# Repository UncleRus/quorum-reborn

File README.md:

# Quorum Reborn

## Russian

[English](#english)

Старая и восстановленная документация для компьютеров ZX Spectrum "Кворум" и "Магик".

### Что такое "Кворум"?

"Кворум" — домашний компьютер, клон ZX Spectrum на советской элементной базе.
Разработан в Свердловске/Екатеринбурге Камилем Каримовым, выпускался заводами
"Вектор", "УОМЗ". Все машины имеют кодер SECAM.

Поддержка "Кворума" встроена в эмуляторы UnrealSpeccy и ZXMAK2.

#### Модели компьютеров

- **Magic-05** — Клон ZX Spectrum 48K с расширенной клавиатурой и портом Centronics.
- **Кворум 64** — Модифицированная версия «Magic-05» с доступным ОЗУ объёмом 64 КБ
   (дополнительные 16 КБ использовались как «теневое» ОЗУ) и измененной адресацией
   дополнительного порта расширенной клавиатуры.
- **Кворум 128** — Клон ZX Spectrum 128K без AY-3-8910. Схема построена на БМК
   КБ01ВГ1-2. В ПЗУ присутствует встроенный тест, монитор и копировщик. Возможность
   работы как в TR-DOS, так и в CP/M. На задней стенке корпуса компьютера располагались
   разъёмы для подключения внешнего блока питания, Kempston и Sinclair джойстиков,
   принтера, магнитофона, телевизора и монитора, а также разъём системной шины для
   подключения внешнего контроллера дисковода.
- **Кворум 128+** — Модификация «Кворум 128» со встроенным 3-дюймовым дисководом,
   контроллером дисковода и звуковым синтезатором AY-3-8910.
- **Кворум БК04** — Выпускался УОМЗ. Клон ZX Spectrum 48K. Имеет кодер SECAM с
   ВЧ-модулятором.
- **Кворум БК05** — Выпускался УОМЗ. Клон ZX Spectrum 48K на БМК КБ01ВГ1-2 и
   однокристальном SECAM-кодере. На плате реализован порт принтера, но отсутствует
   разъем.

### Состав репозитория

- **kicad** - Проекты KiCad для
   - Magic-05,
   - Кворум 64,
   - Кворум 128,
   - Кворум БК04,
   - контроллера дисковода
- **resources** - Старая документация, прошивки, фотографии, софт

### Проекты KiCad

Для работы с ними необходим KiCad версии >= 7.0.
Также в каждом проекте, в подкаталогах /plot лежат схемы, экспортированные в формат PDF.

### Ссылки

https://github.com/atsidaev/quorum-cpm - Исходники CP/M для "Кворума", документация 
по программированию.

## English

Old and restored documentation for ZX Spectrum computers "Quorum" and "Magic".

### What is "Quorum"?

"Quorum" is a home computer, a clone of the ZX Spectrum built with Soviet ICs.
It's developed in Yekaterinburg f.k.a. Sverdlovsk by Kamil Karimov and manufactured by "Vector" and "UOMZ"
factories. All models have built-in SECAM encoder.

Quorum is supported by UnrealSpeccy and ZXMAK2 emulators.

#### The lineup

- **Magic-05** — ZX Spectrum 48K clone with extended keyboard and Centronics port.
- **Quorum 64** — Modified version of "Magic-05" with 64 KB available RAM (additional
   16 KB is used as shadow RAM) and changed addressing of the extended keyboard
   additional port.
- **Quorum 128** — ZX Spectrum 128K clone without the AY-3-8910. The construction 
   is based on KB01VG1-2. The ROM contains a built-in test, monitor and copier.
   It has ability to work in both TR-DOS and CP/M. On the rear side of the computer
   case there were connectors for connecting an external power supply, Kempston and
   Sinclair joysticks, a printer, a tape recorder, a TV and a monitor, as well as a
   system bus connector for connecting an external floppy controller.
- **Quorum 128+** — Quorum 128 modification with a built-in 3-inch drive,
   floppy controller and sound synthesizer AY-3-8910.
- **Quorum БК04** — Produced by UOMZ. ZX Spectrum 48K clone. Has a SECAM encoder with
   RF modulator.
- **Quorum БК05** — Produced by UOMZ. ZX Spectrum 48K clone on BMK KB01VG1-2 and
   single-chip SECAM encoder. The board has a printer port, but no connector.

### Repository contents

- **kicad** - KiCad projects for
   - Magic-05,
   - Quorum 64,
   - Quorum 128,
   - Quorum БК04,
   - Floppy Disk Drive
- **resources** - Old docs, firmware, images, software.

### KiCad Projects

To work with projects you'll need KiCad version >= 7.0.
Also in each project, in the /plot subdirectory there are schematic diagrams 
exported in PDF format.

### Links

https://github.com/atsidaev/quorum-cpm - CP/M sources for Quorum,
development docs.

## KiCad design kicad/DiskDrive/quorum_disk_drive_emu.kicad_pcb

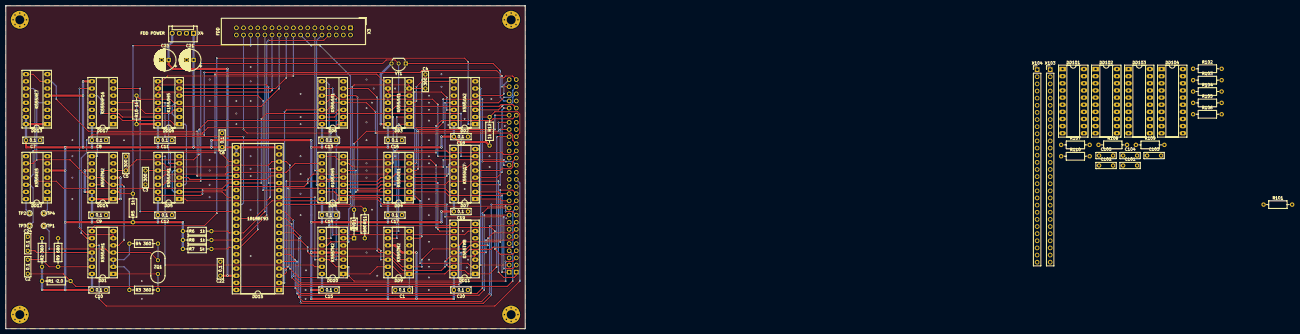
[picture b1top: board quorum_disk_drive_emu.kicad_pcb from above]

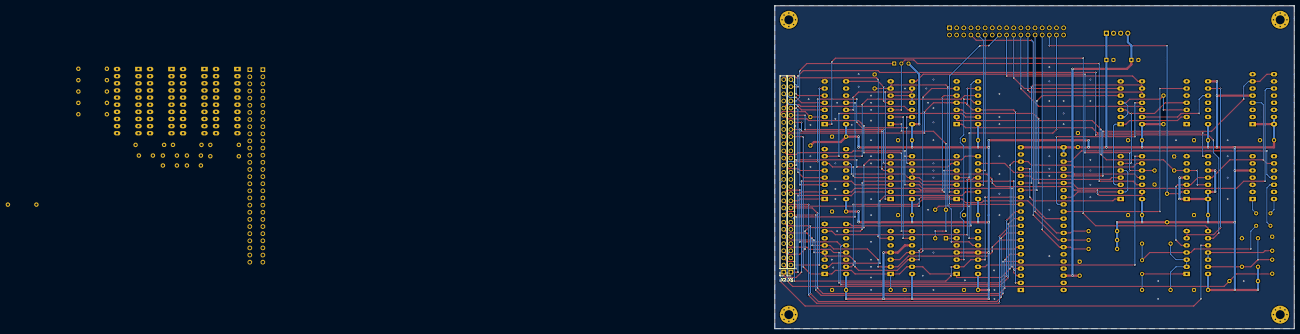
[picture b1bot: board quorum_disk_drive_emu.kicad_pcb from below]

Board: 2 copper layers, 185.0 x 115.0 mm, 85 parts (2 on the bottom side), 141 nets.

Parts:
C1, C2, C6, C7, C8, C9, C10, C11, C12, C13, C14, C15, C16, C17, C18, C19, C20, C22, C24, C102, C103, C104, C105: 0,1; C_Rect_L7.0mm_W2.0mm_P5.00mm
C3, C4, C5: 300; C_Rect_L7.0mm_W2.0mm_P5.00mm
C21, C23: 20,0; CP_Radial_D7.5mm_P2.50mm
C101: 470; C_Rect_L7.0mm_W2.0mm_P5.00mm
DD1: К555ЛН1; DIP-14_W7.62mm_Socket_LongPads
DD2: К555ЛА2; DIP-14_W7.62mm_Socket_LongPads
DD3, DD6: К555ЛЛ1; DIP-14_W7.62mm_Socket_LongPads
DD4: К555ЛЕ1; DIP-14_W7.62mm_Socket_LongPads
DD5: К555ЛИ1; DIP-14_W7.62mm_Socket_LongPads
DD7: К555ИД7; DIP-16_W7.62mm_Socket_LongPads
DD8, DD16: К155ЛН5; DIP-14_W7.62mm_Socket_LongPads
DD9, DD10, DD14: К555ТМ2; DIP-14_W7.62mm_Socket_LongPads
DD11: К555ТМ8; DIP-16_W7.62mm_Socket_LongPads
DD12: К555ИЕ5; DIP-14_W7.62mm_Socket_LongPads
DD13: К555ИЕ7; DIP-16_W7.62mm_Socket_LongPads
DD15: 1818ВГ93; DIP-42_W15.24mm_Socket_LongPads
DD17: К555ИР16; DIP-14_W7.62mm_Socket_LongPads
DD101, DD102, DD103, DD104: К555АП6; DIP-20_W7.62mm_Socket_LongPads
R1: 2,0; R_Axial_DIN0207_L6.3mm_D2.5mm_P10.16mm_Horizontal
R2, R3, R4: 360; R_Axial_DIN0207_L6.3mm_D2.5mm_P10.16mm_Horizontal
R5, R6, R7, R8, R10, R12, R101, R102: 1k; R_Axial_DIN0207_L6.3mm_D2.5mm_P10.16mm_Horizontal
R9, R11: 680; R_Axial_DIN0207_L6.3mm_D2.5mm_P10.16mm_Horizontal
R103, R104, R105, R106, R107, R108, R109, R110: 2k7; R_Axial_DIN0207_L6.3mm_D2.5mm_P10.16mm_Horizontal
TP1, TP2, TP3, TP4: TestPoint; TestPoint_THTPad_D1.5mm_Drill0.7mm
VD1: КД522; D_DO-35_SOD27_P10.16mm_Horizontal
VT1: КТ315; TO-92_Inline_Wide
X1, X2: CONN_28; PinSocket_1x28_P2.54mm_Vertical
X3: FDD; IDC-Header_2x17_P2.54mm_Vertical
X4: FDD POWER; MOLEX-1X4
X103, X104: CONN_28; PinHeader_1x28_P2.54mm_Vertical
ZQ1: 8 МГц (16 МГц); Crystal_HC49-U_Vertical

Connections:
+5V: C6.2, C7.2, C8.2, C9.2, C10.2, C11.2, C12.2, C13.2, C14.2, C15.2, C16.2, C17.2, C18.2, C19.2, C20.2, C21.1, C102.2, C103.2, C104.2, C105.2, DD1.14, DD2.14, DD3.14, DD4.14, DD5.14, DD6.14, DD7.16, DD8.14, DD9.4, DD9.10, DD9.14, DD10.4, DD10.11, DD10.14, DD11.16, DD12.5, DD13.1, DD13.5, DD13.15, DD13.16, DD14.1, DD14.4, DD14.10, DD14.13, DD14.14, DD15.21, DD15.22, DD15.23, DD16.14, DD17.8, DD17.14, DD101.1, DD101.20, DD102.1, DD102.20, DD103.1, DD103.20, DD104.20, R1.1, R2.1, R5.1, R6.1, R7.1, R8.1, R10.1, R12.2, R101.2, R102.1, R103.2, R104.2, R105.2, R106.2, R107.2, R108.2, R109.2, R110.2, VT1.3, X4.1
+12V: C22.2, C23.1, DD15.40, X4.4
/A0: DD15.5, X1.9
/A1: DD15.6, X1.10
/A2: DD7.1, X1.11
/A3: DD7.2, X1.12
/A4: DD7.4, X1.24
/A5: DD4.6, X1.23
/A6: DD4.5, X1.22
/A7: DD7.3, X1.21
/A8: DD2.3, X2.26
/A9: DD1.9, X1.27
/A10: DD2.4, X2.27
/A11: DD2.5, X1.28
/A12: DD2.6, X1.2
/A13: DD2.11, X2.2
/A14: DD4.2, X1.1
/A15: DD4.3, X2.1
/BUFFER/BA0: DD101.18, X103.9
/BUFFER/BA1: DD101.17, X103.10
/BUFFER/BA2: DD101.16, X103.11
/BUFFER/BA3: DD101.15, X103.12
/BUFFER/BA4: DD101.14, X103.24
/BUFFER/BA5: DD101.13, X103.23
/BUFFER/BA6: DD101.12, X103.22
/BUFFER/BA7: DD101.11, X103.21
/BUFFER/BA8: DD102.18, X104.26
/BUFFER/BA9: DD102.17, X103.27
/BUFFER/BA10: DD102.16, X104.27
/BUFFER/BA11: DD102.15, X103.28
/BUFFER/BA12: DD102.14, X103.2
/BUFFER/BA13: DD102.13, X104.2
/BUFFER/BA14: DD102.12, X103.1
/BUFFER/BA15: DD102.11, X104.1
/BUFFER/BD0: DD104.18, R103.1, X104.6
/BUFFER/BD1: DD104.17, R104.1, X104.7
/BUFFER/BD2: DD104.16, R105.1, X104.8
/BUFFER/BD3: DD104.15, R106.1, X104.11
/BUFFER/BD4: DD104.14, R107.1, X104.12
/BUFFER/BD5: DD104.13, R108.1, X104.10
/BUFFER/BD6: DD104.12, R109.1, X104.9
/BUFFER/BD7: DD104.11, R110.1, X104.3
/BUFFER/BK.NMI: DD103.11, X103.4
/BUFFER/K.NMI: DD103.9, R101.1
/BUFFER/~BIORQ: DD103.16, X104.17
/BUFFER/~BLK: DD104.1, R102.2, X103.16
/BUFFER/~BM1: DD103.14, X104.24
/BUFFER/~BMREQ: DD103.15, X104.16
/BUFFER/~BRD: DD103.18, X104.18
/BUFFER/~BRES: DD103.12, X103.20
/BUFFER/~BRFSH: DD103.13, X104.25
/BUFFER/~BWR: DD103.17, X104.19
/BUFFER/~UPS: C101.1, X104.28
/CLK1: DD12.11, DD15.24
/D0: DD9.12, DD11.4, DD15.7, X2.6
/D1: DD9.2, DD11.5, DD15.8, X2.7
/D2: DD15.9, X2.8
/D3: DD15.10, X2.11
/D4: DD11.12, DD15.11, X2.12
/D5: DD11.13, DD15.12, X2.10
/D6: DD15.13, X2.9
/D7: DD10.2, DD10.12, DD15.14, X2.3
/DS0: DD8.13, DD11.2
/DS1: DD8.11, DD11.7
/K.NMI: C2.2, R1.2, X1.4
/MTRON: DD8.1, DD11.15, DD15.32
/RA14: DD2.2, R12.1, X2.20
/SIDE: DD8.4, X3.32
/~BLK: DD8.6, X1.16
/~CSFDC: DD4.11, DD7.11, DD15.3
/~DIR: DD16.8, X3.18
/~DS0: DD8.12, X3.10
/~DS1: DD8.10, X3.12
/~DWR: DD16.12, X3.22
/~EWR: DD16.10, X3.24
/~IND: DD15.35, R8.2, X3.8
/~IORQ: DD7.5, X2.17
/~M1: DD3.12, X2.24
/~MOT: DD8.2, X3.16
/~MREQ: DD3.13, DD4.9, X2.16
/~NMI: DD1.10, X2.14
/~RAMCS: DD8.8, X2.4
/~RD: DD4.8, DD4.12, DD15.4, X2.18
/~RDD: DD14.2, R5.2, X3.30
/~RES: C1.1, DD5.9, DD9.1, DD9.13, DD10.1, DD11.1, DD15.19, X1.20
/~ROMCS: VT1.1, X1.25
/~SIDE: DD8.3, DD11.10
/~STEP: DD16.6, X3.20
/~TR00: DD15.34, R6.2, X3.26
/~TRD: DD9.8, X2.23
/~UPS: DD9.6, X2.28
/~WR: DD6.4, DD6.9, DD6.12, DD15.2, X2.19
/~WRPR: DD15.36, R7.2, X3.28
GND: C1.2, C3.2, C4.1, C5.2, C6.1, C7.1, C8.1, C9.1, C10.1, C11.1, C12.1, C13.1, C14.1, C15.1, C16.1, C17.1, C18.1, C19.1, C20.1, C21.2, C22.1, C23.2, C24.1, C101.2, C102.1, C103.1, C104.1, C105.1, DD1.7, DD2.7, DD3.7, DD4.7, DD5.7, DD6.7, DD7.8, DD8.7, DD9.7, DD10.7, DD11.8, DD12.2, DD12.3, DD12.10, DD13.8, DD13.10, DD13.14, DD14.7, DD15.20, DD15.37, DD16.7, DD17.1, DD17.5, DD17.7, DD101.10, DD101.19, DD102.10, DD102.19, DD103.10, DD103.19, DD104.10, DD104.19, R9.2, X1.6, X1.7, X1.14, X3.1, X3.3, X3.5, X3.7, X3.9, X3.11, X3.13, X3.15, X3.17, X3.19, X3.21, X3.23, X3.25, X3.27, X3.29, X3.31, X3.33, X4.2, X4.3, X103.6, X103.7, X103.14
unnamed: C2.1, DD1.13, R2.2, R9.1
unnamed: C3.1, DD3.8, DD5.10
unnamed: C4.2, DD3.6, DD10.10
unnamed: C5.1, DD6.2, DD14.5, DD14.12
unnamed: C24.2, DD1.11, DD1.12
unnamed: DD1.1, R3.2, ZQ1.1
unnamed: DD1.2, DD1.3, R3.1, R4.2
unnamed: DD1.4, R4.1, TP1.1, ZQ1.2
unnamed: DD1.5, DD12.9, DD13.4, DD14.3, DD14.11
unnamed: DD1.6, DD17.9
unnamed: DD1.8, DD2.1
unnamed: DD2.8, DD3.4
unnamed: DD2.12, DD3.9, DD4.1
unnamed: DD3.1, R11.2, VD1.2
unnamed: DD3.2, DD9.9
unnamed: DD3.3, DD5.12, VT1.2
unnamed: DD3.5, DD3.10, DD3.11
unnamed: DD4.4, DD7.6
unnamed: DD4.10, DD5.13
unnamed: DD4.13, DD8.5
unnamed: DD5.11, DD8.9
unnamed: DD6.5, DD7.15
unnamed: DD6.6, DD9.3, DD9.11
unnamed: DD6.10, DD7.10
unnamed: DD6.13, DD7.7
unnamed: DD6.11, DD10.3
unnamed: DD10.6, VD1.1
unnamed: DD10.9, R11.1
unnamed: DD5.8, DD10.13
unnamed: DD6.8, DD11.9
unnamed: DD12.1, TP4.1
unnamed: DD12.12, TP3.1
unnamed: DD12.14, TP2.1
unnamed: DD13.7, DD13.9, DD15.26
unnamed: DD6.3, DD13.11, DD15.27
unnamed: DD6.1, DD14.8
unnamed: DD15.15, DD16.5
unnamed: DD15.16, DD16.9
unnamed: DD5.4, DD15.17
unnamed: DD5.1, DD15.18
unnamed: DD5.2, DD5.5, DD15.29
unnamed: DD15.30, DD16.11
unnamed: DD15.31, DD17.6
unnamed: DD5.3, DD16.1, DD17.2
unnamed: DD16.2, DD16.4, DD17.3, R10.2
unnamed: DD5.6, DD16.3, DD17.4
unnamed: DD16.13, DD17.10

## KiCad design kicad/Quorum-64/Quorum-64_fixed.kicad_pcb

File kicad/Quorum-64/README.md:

## Схема Кворум 64

  - Этот каталог содержит оригинальную схему "Кворум 64" с исправленными ошибками без модификаций
  - Подкаталог `fix-brightness` содержит вариант схемы "Кворум 64" с исправленной ошибкой атрибута яркости у черного

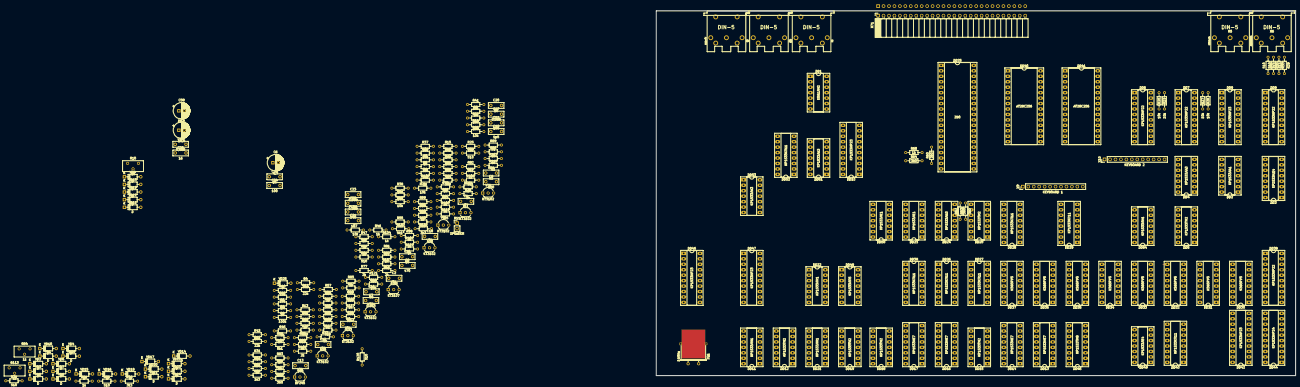
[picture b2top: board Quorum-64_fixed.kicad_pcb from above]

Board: 2 copper layers, 298.0 x 170.0 mm, 250 parts (1 on the bottom side), 293 nets.

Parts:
*C59: 240; C_Rect_L7.0mm_W2.5mm_P5.00mm
*DD48: КР1533ЛЕ4; DIP-14_W7.62mm_Socket_LongPads
C1: 0,1; C_Rect_L7.0mm_W2.5mm_P5.00mm
C2, C3: 0,33; C_Rect_L7.0mm_W2.5mm_P5.00mm
C6: 4.7; CP_Radial_D7.5mm_P2.50mm
C7: 0,033; C_Rect_L7.0mm_W2.5mm_P5.00mm
C8, C10, C12: 470; C_Rect_L7.0mm_W2.5mm_P5.00mm
C9, C11, C13, C24: 100; C_Rect_L7.0mm_W2.5mm_P5.00mm
C14: 82; C_Rect_L7.0mm_W2.5mm_P5.00mm
C15, C20, C21, C25, C26: 16; C_Rect_L7.0mm_W2.5mm_P5.00mm
C16: 56; C_Rect_L7.0mm_W2.5mm_P5.00mm
C17, C18, C22, C23: 0,068; C_Rect_L7.0mm_W2.5mm_P5.00mm
C19: 1p5; C_Rect_L7.0mm_W2.5mm_P5.00mm
C57: 10,0; CP_Radial_D7.5mm_P2.50mm
C58: 68,0; CP_Radial_D7.5mm_P2.50mm
DD1: К561ЛН2; DIP-14_W7.62mm_Socket_LongPads
DD2: КР1533ЛА1; DIP-14_W7.62mm_Socket_LongPads
DD3: КР1533ИД4; DIP-16_W7.62mm_Socket_LongPads
DD4, DD24, DD51, DD53: КР1533ЛА3; DIP-14_W7.62mm_Socket_LongPads
DD5, DD12, DD15, DD18, DD19, DD20: КР1533ТМ2; DIP-14_W7.62mm_Socket_LongPads
DD6, DD7, DD8, DD38: КР1533ИР22; DIP-20_W7.62mm_Socket_LongPads
DD9, DD10, DD42, DD46, DD47: КР1533ИР23; DIP-20_W7.62mm_Socket_LongPads
DD11, DD21, DD54: КР1533ЛН1; DIP-14_W7.62mm_Socket_LongPads
DD13, DD14, DD16, DD17: КР1533ИЕ7; DIP-16_W7.62mm_Socket_LongPads
DD22: КР1533ЛИ1; DIP-14_W7.62mm_Socket_LongPads
DD23, DD50: КР1533ЛЕ1; DIP-14_W7.62mm_Socket_LongPads
DD25: Z80; DIP-40_W15.24mm_Socket_LongPads
DD26, DD27, DD28, DD29, DD39, DD43, DD52: КР1533КП11; DIP-16_W7.62mm_Socket_LongPads
DD30, DD31, DD32, DD33, DD34, DD35, DD36, DD37: К565РУ5; DIP-16_W7.62mm_Socket_LongPads
DD40, DD41: AT28C256; DIP-28_W15.24mm_Socket_LongPads
DD44: КР1533ИР24; DIP-20_W7.62mm_Socket_LongPads
DD45: КР1533ТМ8; DIP-16_W7.62mm_Socket_LongPads
DD49: КР1533ЛП5; DIP-14_W7.62mm_Socket_LongPads
R1: 1M; R_Axial_DIN0204_L3.6mm_D1.6mm_P7.62mm_Horizontal
R2: 3M; R_Axial_DIN0204_L3.6mm_D1.6mm_P7.62mm_Horizontal
R3, R46, R47, R49, R67, R68, R69, R75, R79, R83, R90, R91, R92, R96, R97, R98, R102, R103, R104, R105, R115, R119: 1k; R_Axial_DIN0204_L3.6mm_D1.6mm_P7.62mm_Horizontal
R4, R36, R54, R55, R110: 3k3; R_Axial_DIN0204_L3.6mm_D1.6mm_P7.62mm_Horizontal
R5, R11, R12, R13: 22k; R_Axial_DIN0204_L3.6mm_D1.6mm_P7.62mm_Horizontal
R6, R45, R48, R52, R56, R71, R72, R73, R77, R85, R94, R99, R100, R101: 2k; R_Axial_DIN0204_L3.6mm_D1.6mm_P7.62mm_Horizontal
R7, R9, R14, R15, R16, R17, R18, R19, R20, R21, R22, R23, R24, R25, R26, R27, R28, R37, R38, R39, R40, R41, R42, R43, R44, R122: 10k; R_Axial_DIN0204_L3.6mm_D1.6mm_P7.62mm_Horizontal
R8: 100k; R_Axial_DIN0204_L3.6mm_D1.6mm_P7.62mm_Horizontal
R10, R84, R113: 1k; Potentiometer_Bourns_3296Y_Vertical
R29, R30, R31, R32, R33, R34, R35, R51, R53, R57, R58, R59, R86, R87, R88, R95, R112, R114, R120: 510; R_Axial_DIN0204_L3.6mm_D1.6mm_P7.62mm_Horizontal
R50, R70, R80: 820; R_Axial_DIN0204_L3.6mm_D1.6mm_P7.62mm_Horizontal
R60, R61, R62, R63, R64, R65, R66, R116, R117, R121: 360; R_Axial_DIN0204_L3.6mm_D1.6mm_P7.62mm_Horizontal
R74: 22k*; R_Axial_DIN0204_L3.6mm_D1.6mm_P7.62mm_Horizontal
R76, R93: 3k9; R_Axial_DIN0204_L3.6mm_D1.6mm_P7.62mm_Horizontal
R78: 1k3; R_Axial_DIN0204_L3.6mm_D1.6mm_P7.62mm_Horizontal
R81, R82, R106, R107, R108: 5k1; R_Axial_DIN0204_L3.6mm_D1.6mm_P7.62mm_Horizontal
R89, R109, R118: 51; R_Axial_DIN0204_L3.6mm_D1.6mm_P7.62mm_Horizontal
R111: 1k5; R_Axial_DIN0204_L3.6mm_D1.6mm_P7.62mm_Horizontal
R123: 5k1*; R_Axial_DIN0204_L3.6mm_D1.6mm_P7.62mm_Horizontal
VD1, VD2, VD3, VD4, VD5, VD6, VD7, VD8, VD9, VD10, VD11, VD12, VD13, VD14, VD15, VD16, VD17, VD18, VD19, VD20, VD21, VD22, VD23, VD24, VD25, VD26: D; D_DO-35_SOD27_P7.62mm_Horizontal
VT1: KT3107; TO-92_Inline_Wide
VT2, VT3, VT4, VT5, VT9: KT3102; TO-92_Inline_Wide
VT6, VT7: КТ3102; TO-92_Inline_Wide
VT8: BF245; TO-92_Inline_Wide
X1: IN; DIN5-RA-PTH
X2: OUT; DIN5-RA-PTH
X3: RGB+TV; DIN5-RA-PTH
X5: SINCLAIR; DIN5-RA-PTH
X6: KEMPSTON; DIN5-RA-PTH
X9: KEYBOARD 1; PinHeader_1x12_P2.54mm_Vertical
X10: KEYBOARD 2; PinHeader_1x12_P2.54mm_Vertical
X11: SPEAKER; PinHeader_1x02_P2.54mm_Vertical
X71: EXPANSION TOP; PinSocket_1x28_P2.54mm_Horizontal
X72: EXPANSION BOTTOM; PinSocket_1x28_P2.54mm_Horizontal
ZQ1: 14MHz; Crystal_HC49-U_Horizontal_1EP_style2

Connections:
+5V: *DD48.14, C58.1, DD1.14, DD2.1, DD2.2, DD2.4, DD2.14, DD3.16, DD4.13, DD4.14, DD5.1, DD5.4, DD5.10, DD5.13, DD5.14, DD6.11, DD6.20, DD7.11, DD7.20, DD8.11, DD8.20, DD9.20, DD10.20, DD11.14, DD12.1, DD12.4, DD12.10, DD12.13, DD12.14, DD13.4, DD13.11, DD13.16, DD14.4, DD14.11, DD14.16, DD15.1, DD15.14, DD16.4, DD16.9, DD16.16, DD17.4, DD17.9, DD17.16, DD18.4, DD18.10, DD18.14, DD19.14, DD20.1, DD20.4, DD20.11, DD20.12, DD20.14, DD21.14, DD22.14, DD23.14, DD24.14, DD25.11, DD26.16, DD27.14, DD27.16, DD28.16, DD29.16, DD30.16, DD31.16, DD32.16, DD33.16, DD34.16, DD35.16, DD36.16, DD37.16, DD38.20, DD39.10, DD39.13, DD39.16, DD40.1, DD40.27, DD40.28, DD41.1, DD41.27, DD41.28, DD42.20, DD43.16, DD44.1, DD44.2, DD44.3, DD44.20, DD45.16, DD46.20, DD47.20, DD49.14, DD50.14, DD51.14, DD52.13, DD52.14, DD52.16, DD53.14, DD54.14, R9.2, R11.2, R12.2, R13.2, R14.2, R15.2, R16.2, R17.2, R18.2, R19.2, R20.2, R21.2, R22.2, R23.2, R24.2, R25.2, R26.2, R27.2, R28.2, R37.2, R38.2, R39.2, R40.2, R41.2, R42.2, R43.2, R44.2, R46.2, R47.2, R55.1, R59.1, R67.2, R68.2, R69.2, R84.1, R86.2, R91.2, R105.1, R118.2, R121.2, VT1.1, VT3.3, VT4.3, VT5.3, VT9.3, X6.6, X72.3
/A0: DD3.13, DD25.30, DD28.2, DD40.10, DD41.10, X72.9
/A1: DD2.10, DD25.31, DD28.5, DD40.9, DD41.9, X72.10
/A2: DD25.32, DD28.11, DD40.8, DD41.8, X72.11
/A3: DD2.12, DD25.33, DD28.14, DD40.7, DD41.7, X72.12
/A4: DD2.13, DD25.34, DD29.2, DD40.6, DD41.6, X72.24
/A5: DD25.35, DD29.5, DD40.5, DD41.5, X72.23
/A6: DD25.36, DD29.11, DD40.4, DD41.4, X72.22
/A7: DD3.3, DD25.37, DD28.3, DD40.3, DD41.3, X72.21
/A8: DD25.38, DD28.6, DD40.25, DD41.25, VD1.1, X71.26
/A9: DD25.39, DD28.10, DD40.24, DD41.24, VD7.1, X72.27
/A10: DD25.40, DD28.13, DD40.21, DD41.21, VD5.1, X71.27
/A11: DD25.1, DD29.3, DD40.23, DD41.23, VD4.1, X72.28
/A12: DD25.2, DD29.6, DD40.2, DD41.2, VD3.1, X72.2
/A12*: VD3.2, X5.6, X9.6
/A13: DD11.13, DD25.3, DD29.10, DD40.20, DD40.26, DD41.26, VD6.1, X71.2
/A14: DD23.11, DD25.4, DD29.14, VD2.1, X72.1
/A15: DD23.12, DD25.5, DD29.13, VD8.1, X71.1
/B: *DD48.11, DD43.4, DD49.1, R71.1, VD10.2
/BB: DD10.2, R71.2
/BG: DD10.6, R73.2
/BI: DD46.3, DD49.3, DD52.3, DD52.11
/BORD: DD20.6, DD43.15
/BR: DD10.5, R72.2
/BT: DD46.9, R102.1
/CLK: DD21.6, DD25.6, R59.2
/COPY: DD1.6, DD6.17, R8.2, X2.4
/D0: DD6.2, DD7.2, DD8.2, DD9.3, DD10.3, DD25.14, DD30.2, DD38.2, DD40.11, DD41.11, R37.1, X71.6
/D1: DD6.5, DD7.5, DD8.5, DD9.4, DD10.4, DD25.15, DD31.2, DD38.5, DD40.12, DD41.12, R38.1, X71.7
/D2: DD6.6, DD7.6, DD8.6, DD9.7, DD10.7, DD25.12, DD32.2, DD38.6, DD40.13, DD41.13, R39.1, X71.8
/D3: DD6.9, DD7.9, DD8.9, DD9.8, DD10.8, DD25.8, DD33.2, DD38.9, DD40.15, DD41.15, R40.1, X71.11
/D4: DD6.12, DD7.12, DD8.12, DD9.13, DD10.13, DD25.7, DD34.2, DD38.12, DD40.16, DD41.16, R41.1, X71.12
/D5: DD6.15, DD7.15, DD8.15, DD9.14, DD10.14, DD25.9, DD35.2, DD38.15, DD40.17, DD41.17, R42.1, X71.10
/D6: DD6.16, DD7.16, DD8.16, DD9.17, DD10.17, DD25.10, DD36.2, DD38.16, DD40.18, DD41.18, R43.1, X71.9
/D7: DD6.19, DD7.19, DD8.19, DD9.18, DD10.18, DD25.13, DD37.2, DD38.19, DD40.19, DD41.19, R44.1, X71.3
/DC0: DD12.12, DD13.3, DD21.13, DD22.2, DD22.4
/DC1: DD13.2, DD21.11, DD22.5, DD28.15, DD29.15
/DC2: DD13.6, DD21.9, DD39.1
/FL: DD1.8, DD4.10, R2.2
/G: *DD48.9, DD43.9, DD49.9, R73.1, VD12.2
/GI: DD47.3, DD49.8, DD51.4, DD51.5, DD52.6
/GT: DD47.9, R104.1
/H0: DD13.7, DD26.2
/H1: DD14.3, DD19.3, DD26.5
/H2: DD11.9, DD11.11, DD14.2, DD26.11
/H3: DD14.6, DD15.3, DD15.11, DD26.14
/H4: DD14.7, DD15.2, DD15.12, DD19.2, DD27.2
/HBL: DD19.4, DD19.6, DD50.11
/HBR: DD15.8, DD15.10, DD23.2, R53.2
/KEMP0: DD8.3, R29.1, X6.3
/KEMP1: DD8.4, R30.1, X6.2
/KEMP2: DD8.7, R31.1, X6.1
/KEMP3: DD8.8, R32.1, X6.4
/KEMP4: DD8.13, R33.1, X6.5
/KINV: DD5.3, R11.1, X9.10
/KNMI: X9.9, X72.4
/KSPK: DD5.11, R12.1, X9.11
/K_D0: DD6.3, R14.1, X5.5, X10.2
/K_D0*: DD7.3, R21.1, X10.1
/K_D1: DD6.4, R15.1, X5.4, X10.4
/K_D1*: DD7.4, R22.1, X10.3
/K_D2: DD6.7, R16.1, X5.1, X10.5
/K_D2*: DD7.7, R23.1, X10.8
/K_D3: DD6.8, R17.1, X5.3, X10.6
/K_D3*: DD7.8, R24.1, X10.9
/K_D4: DD6.13, R18.1, X5.2, X10.7
/K_D4*: DD7.13, R25.1, X10.10
/K_D5*: DD7.14, R26.1, X10.11
/MA0: DD26.4, DD28.4, DD30.13, DD31.13, DD32.13, DD33.13, DD34.13, DD35.13, DD36.13, DD37.13
/MA1: DD26.7, DD28.7, DD30.12, DD31.12, DD32.12, DD33.12, DD34.12, DD35.12, DD36.12, DD37.12
/MA2: DD26.9, DD28.9, DD30.11, DD31.11, DD32.11, DD33.11, DD34.11, DD35.11, DD36.11, DD37.11
/MA3: DD26.12, DD28.12, DD30.10, DD31.10, DD32.10, DD33.10, DD34.10, DD35.10, DD36.10, DD37.10
/MA4: DD27.4, DD29.4, DD30.5, DD31.5, DD32.5, DD33.5, DD34.5, DD35.5, DD36.5, DD37.5
/MA5: DD27.7, DD29.7, DD30.6, DD31.6, DD32.6, DD33.6, DD34.6, DD35.6, DD36.6, DD37.6
/MA6: DD27.9, DD29.9, DD30.7, DD31.7, DD32.7, DD33.7, DD34.7, DD35.7, DD36.7, DD37.7
/MA7: DD27.12, DD29.12, DD30.9, DD31.9, DD32.9, DD33.9, DD34.9, DD35.9, DD36.9, DD37.9
/MD0: DD30.14, DD38.3, DD42.3, DD44.7
/MD1: DD31.14, DD38.4, DD42.4, DD44.13
/MD2: DD32.14, DD38.7, DD42.7, DD44.6
/MD3: DD33.14, DD38.8, DD42.8, DD44.14
/MD4: DD34.14, DD38.13, DD42.13, DD44.5
/MD5: DD35.14, DD38.14, DD42.14, DD44.15
/MD6: DD36.14, DD38.17, DD42.17, DD44.4
/MD7: DD37.14, DD38.18, DD42.18, DD44.16
/MIC: C2.2, DD10.9, R10.1, X2.1
/OSC: DD12.2, DD12.6, DD12.11
/OUT: C2.1, R3.2, X2.3
/R: *DD48.10, DD43.7, DD49.5, R72.1, VD11.2
/RAS: DD12.8, DD21.1, DD24.10
/RI: DD46.13, DD49.6, DD51.1, DD51.2
/RT: DD46.19, R103.1
/S0: *C59.1, DD21.4, DD21.5, DD26.1, DD27.1, DD28.1, DD29.1
/SCR: DD22.8, DD44.19
/SPK: DD10.12, R10.2, R48.1, X2.5
/UINV: DD5.5, DD49.2, DD49.4, DD49.10, DD50.9, VD22.1
/USPK: DD5.9, R45.1
/V0: DD16.3, DD39.2, DD52.1, R80.1
/V0V6: DD26.6, DD39.4
/V1: DD16.2, DD39.5
/V1V7: DD26.10, DD39.7
/V2: DD16.6, DD22.12
/V3: DD16.7, DD19.11, DD27.5
/V4: DD17.3, DD19.12, DD27.11
/V5: DD17.2, DD26.3
/V6: DD17.6, DD18.3, DD18.11, DD39.3, DD39.11
/V7: DD17.7, DD18.2, DD18.12, DD39.6, DD39.14
/V20: DD22.11, DD26.13
/V61: DD27.3, DD39.9
/V71: DD27.6, DD39.12
/VBL: DD19.8, DD19.10, DD50.12, DD51.12
/VBR: DD18.9, DD23.3, R57.2, VD9.1
/VSYN: C7.1, DD18.5
/WRBUF: DD22.3, DD38.11
/Y: *DD48.6, DD47.13
/Y0: DD50.1, VD16.1, VD17.1, VD18.1
/Y1: DD50.10, R121.1, VD13.2, VD14.2, VD15.2
/YT: DD47.19, DD50.6, DD50.8
/~BL: DD50.13, VD10.1, VD11.1, VD12.1, VD21.1
/~BUSRQ: DD25.25, R69.1
/~CAS: DD21.12, DD30.15, DD31.15, DD32.15, DD33.15, DD34.15, DD35.15, DD36.15, DD37.15
/~DC1: DD20.10, DD21.10, DD22.1, DD26.15, DD27.15
/~DC2: DD20.3, DD21.8, DD22.10, DD22.13, DD42.11
/~GI: DD51.6, DD52.5
/~HALT: DD25.18, X71.15
/~HSYN: DD15.5, DD16.5, DD19.1, VD19.1, VD25.1
/~INT: DD25.16, R60.2, X71.13
/~IORQ: DD25.20, R65.1, R66.1, X71.17
/~IORQE: DD2.5, R65.2, X72.13
/~M1: DD25.27, X71.24
/~MREQ: DD25.19, R64.1, X71.16
/~MREQE: DD23.6, DD23.8, R64.2, X71.22
/~NMI: DD25.17, R68.1, X71.14
/~OSC: DD12.5, DD13.5, DD44.12, DD45.9, DD46.11, DD47.11
/~PDKEY: DD3.9, DD7.1
/~PKEM: DD3.10, DD8.1
/~PKEY: DD3.11, DD6.1
/~POUT: DD3.5, DD10.11
/~RAS: DD21.2, DD21.3, DD30.4, DD31.4, DD32.4, DD33.4, DD34.4, DD35.4, DD36.4, DD37.4
/~RD: DD3.15, DD23.9, DD25.21, X71.18
/~RDRAM: DD38.1, R62.2, X71.4
/~RDROM: DD40.22, DD41.22, R63.2, X72.25
/~RDY: DD8.18, R36.2
/~RES: C6.1, DD25.26, R13.1, X9.12, X72.20
/~RFSH: DD25.28, X71.25
/~RI: DD51.3, DD52.2, DD52.10
/~UINV: DD5.2, DD5.6, DD50.5
/~UPS: DD54.1, R91.1, X71.28
/~VSYN: DD18.6, DD19.13, VD20.1
/~WAIT: DD25.24, R67.1, X71.21
/~WERAM: DD20.9, DD30.3, DD31.3, DD32.3, DD33.3, DD34.3, DD35.3, DD36.3, DD37.3
/~WR: DD4.12, DD23.5, DD25.22, X71.19
/~WR00: DD3.6, DD4.5
/~WR01: DD3.4, DD4.1, DD9.11
GND: *C59.2, *DD48.2, *DD48.7, *DD48.13, C6.2, C12.2, C13.2, C17.2, C18.2, C20.2, C22.2, C23.2, C24.2, C57.2, C58.2, DD1.7, DD2.7, DD3.8, DD4.7, DD5.7, DD6.10, DD7.10, DD8.10, DD9.1, DD9.10, DD10.1, DD10.10, DD11.7, DD12.7, DD13.8, DD14.8, DD15.7, DD16.1, DD16.8, DD16.10, DD16.14, DD16.15, DD17.1, DD17.8, DD17.10, DD17.14, DD17.15, DD18.7, DD19.7, DD20.7, DD21.7, DD22.7, DD23.7, DD24.7, DD25.29, DD26.8, DD27.8, DD27.10, DD28.8, DD29.8, DD30.8, DD31.8, DD32.8, DD33.8, DD34.8, DD35.8, DD36.8, DD37.8, DD38.10, DD39.8, DD39.15, DD40.14, DD41.14, DD42.1, DD42.10, DD43.8, DD44.10, DD45.8, DD46.1, DD46.10, DD47.1, DD47.10, DD49.7, DD50.7, DD51.7, DD52.8, DD53.7, DD54.7, R3.1, R29.2, R30.2, R31.2, R32.2, R33.2, R34.2, R35.2, R36.1, R51.1, R52.1, R54.2, R56.1, R61.2, R70.1, R84.2, R87.2, R90.1, R96.1, R97.1, R98.1, R111.1, R112.1, R113.2, R115.1, R116.1, R119.1, R123.1, X1.2, X1.6, X2.2, X2.6, X3.2, X3.6, X10.12, X11.2, X72.6, X72.7, X72.14
unnamed: *DD48.1, DD43.12, R70.2
unnamed: *DD48.5, *DD48.8
unnamed: *DD48.3, *DD48.4, *DD48.12
unnamed: C1.1, R1.2
unnamed: C1.2, DD1.9, DD1.10
unnamed: C3.1, X1.3
unnamed: C3.2, R4.1
unnamed: C7.2, DD24.12, R61.1
unnamed: C8.1, DD11.8
unnamed: C8.2, DD15.4, R52.2, R53.1
unnamed: C9.1, DD13.14, DD14.14, R51.2
unnamed: C9.2, DD15.9
unnamed: C10.1, R122.2, VD26.2
unnamed: C10.2, DD18.1
unnamed: C11.1, DD16.11, DD17.11, R54.1, R55.2
unnamed: C11.2, DD18.8
unnamed: C12.1, DD20.2, R58.1
unnamed: C13.1, R88.1, VT9.2
unnamed: C14.1, R74.1, R75.2
unnamed: C14.2, R74.2, R81.1, R82.1, R83.2
unnamed: C15.1, DD53.12, R81.2, VD23.2
unnamed: C15.2, DD53.10, R82.2, VD24.2, VD25.2
unnamed: C16.1, R85.2
unnamed: C16.2, R86.1, R87.1, R88.2, R92.2, R93.2, R94.2, R95.2, R120.2, VD19.2, VD20.2
unnamed: C17.1, C19.1, R109.1, R110.2
unnamed: C18.1, R110.1, R111.2, VT6.2
unnamed: C19.2, C21.2, VT6.3
unnamed: C20.1, C21.1, C25.2, R112.2, VT6.1
unnamed: C22.1, R113.3, R114.2
unnamed: C23.1, R109.2, R113.1, R117.2, R118.1, VT8.3
unnamed: C24.1, R116.2, VT7.1, VT8.2
unnamed: C25.1, R114.1, R115.2, VT7.2
unnamed: C26.1, R89.2, R90.2, X3.1
unnamed: C26.2, R117.1, VT7.3
unnamed: C57.1, R83.1, R84.3
unnamed: DD1.1, R4.2, R5.1
unnamed: DD1.2, R5.2, R6.1
unnamed: DD1.3, R6.2, R7.1, R8.1
unnamed: DD1.4, DD1.5
unnamed: DD1.11, DD1.12
unnamed: DD1.13, R1.1, R2.1
unnamed: DD2.6, DD2.9
unnamed: DD2.8, DD3.2, DD3.14
unnamed: DD3.1, DD4.11
unnamed: DD4.2, DD4.6
unnamed: DD4.3, DD4.4
unnamed: DD4.8, DD49.12
unnamed: DD4.9, DD42.19
unnamed: DD5.8, DD5.12
unnamed: DD6.14, R19.1
unnamed: DD6.18, R20.1
unnamed: DD7.17, R27.1
unnamed: DD7.18, R28.1
unnamed: DD8.14, R34.1
unnamed: DD8.17, R35.1
unnamed: DD11.1, R50.1, ZQ1.1
unnamed: DD11.2, DD11.3
unnamed: DD11.4, DD11.5, ZQ1.2
unnamed: DD11.6, DD12.3, R50.2
unnamed: DD11.10, R122.1, VD26.1
unnamed: DD11.12, DD41.20
unnamed: DD13.12, DD14.5
unnamed: DD14.12, DD15.13
unnamed: DD16.12, DD17.5
unnamed: DD17.12, DD18.13
unnamed: DD20.13, DD24.8
unnamed: DD22.6, DD22.9
unnamed: DD23.1, R58.2
unnamed: DD23.4, DD24.9
unnamed: DD23.10, DD24.2, DD24.5
unnamed: DD23.13, DD24.1
unnamed: DD24.3, DD24.4, R63.1
unnamed: DD24.6, R62.1
unnamed: DD24.11, R60.1
unnamed: DD27.13, DD54.2
unnamed: DD42.2, DD43.2
unnamed: DD42.5, DD43.5
unnamed: DD42.6, DD43.11
unnamed: DD42.9, DD43.3
unnamed: DD42.12, DD43.6
unnamed: DD42.15, DD43.10
unnamed: DD42.16, DD43.13, DD43.14
unnamed: DD43.1, DD49.11
unnamed: DD44.17, DD45.4
unnamed: DD45.2, DD45.5
unnamed: DD45.10, DD45.13
unnamed: DD45.7, DD45.12
unnamed: DD45.15, DD49.13
unnamed: DD46.2, DD46.4
unnamed: DD46.5, DD46.7
unnamed: DD46.6, DD46.8
unnamed: DD46.12, DD46.14
unnamed: DD46.15, DD46.17
unnamed: DD46.16, DD46.18
unnamed: DD47.2, DD47.4
unnamed: DD47.5, DD47.7
unnamed: DD47.6, DD47.8
unnamed: DD47.12, DD47.14
unnamed: DD47.15, DD47.17
unnamed: DD47.16, DD47.18
unnamed: DD50.2, DD50.3, DD50.4
unnamed: DD51.8, DD52.15
unnamed: DD51.9, DD51.10, DD51.11
unnamed: DD52.4, R76.1
unnamed: DD52.7, R77.1
unnamed: DD52.9, R78.1
unnamed: DD52.12, R79.1
unnamed: DD53.1, DD53.9, DD53.11
unnamed: DD53.2, DD53.6, VD23.1
unnamed: DD53.3, DD53.4, R85.1, VD24.1
unnamed: DD53.5, DD53.8, DD53.13
unnamed: R7.2, R9.1, R10.3
unnamed: R45.2, R46.1, VT1.2
unnamed: R47.1, VT1.3, VT2.3
unnamed: R48.2, VT2.2
unnamed: R49.1, VT2.1
unnamed: R49.2, X11.1
unnamed: R56.2, R57.1, VD9.2
unnamed: R89.1, VT9.1
unnamed: R92.1, VD21.2
unnamed: R96.2, VT3.1, X3.4
unnamed: R97.2, VT4.1, X3.3
unnamed: R98.2, VT5.1, X3.5
unnamed: R99.1, VD15.1, VD18.2
unnamed: R100.1, VD14.1, VD17.2
unnamed: R94.1, R100.2, R103.2, R107.2, VT4.2
unnamed: R101.1, VD13.1, VD16.2
unnamed: R93.1, R101.2, R102.2, R106.2, VT3.2
unnamed: R95.1, R99.2, R104.2, R108.2, VT5.2
unnamed: R105.2, R106.1, R107.1, R108.1, VD22.2
unnamed: R119.2, R120.1, VT8.1
unnamed: R75.1, R76.2, R77.2, R78.2, R79.2, R80.2, R123.2
unnamed: VD1.2, X9.8
unnamed: VD2.2, X9.7
unnamed: VD4.2, X9.5
unnamed: VD5.2, X9.4
unnamed: VD6.2, X9.3
unnamed: VD7.2, X9.2
unnamed: VD8.2, X9.1

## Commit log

2019-12-15 Initial upload
2019-12-28 Комментарии к reborn, мелкие правки в q64
2019-12-28 reborn plot
2019-12-28 Добавлен вариант прошивки Magic-05, в reborn добавлены блокирующие C
2019-12-30 Описание портов приведено в удобочитаемый вид
2019-12-30 Исправлена ошибка в KiCad схеме Magic-05
2019-12-30 Краткое описание БК-04
2019-12-31 Исправлена ошибка в KiCad схеме Кворум 64
2019-12-31 Мелкие правки KiCad и README
2019-12-31 Исправлена распиновка разъема расширения в KiCad схеме Кворума 64
2019-12-31 Слот расширения в схеме Magic-05 проверен по реальному компьютеру
2020-01-03 Исправлены ошибки в KiCad схемах M-05, Q-64
2020-01-07 Добавлен KiCad проект Кворума-128
2020-01-07 Удалил новодел
2020-01-07 Правка README
2020-01-07 Удалил мусор
2020-01-08 Добавил перемычки в схему Q128
2020-01-08 Мелкие правки в схемах Q64 и M05
2020-01-08 Исправлено начертание разъемов в схемах
2020-01-12 Q128: исправлены ошибки в схеме, M06: добавлен ROM и схема в другом формате
2020-01-12 M05: вариант ПЗУ
2020-01-12 Q64: Добавлена заметка Caro
2020-01-15 KiCad-проект Кворум БК-04
2020-01-15 v1.1
2020-01-18 BK04: Исправлены ошибки, добавлен вариант с модификациями
2020-01-18 BK04: Добавлен README
2020-01-18 Исправлена ошибка нумерации выводов РУ5
2020-01-18 M05, Q64: исправлены ошибки подключения RAM
2020-01-21 FDD: KiCad проект контроллера FDD
2020-01-21 Мелкие правки
2020-01-21 DD: Схема буфера и контроллера дисковода
2020-01-22 DDemu: исправлены ошибки в схеме и буфере, сгененрирован PDF
2020-01-31 BK04: мелкие правки
2020-02-22 Q64: добавлен вариант модификаций, DD: плата
2020-04-24 Fix #1
2020-11-30 Обновлены УГО разъемов, исправлены множественные ошибки в схемах клавиатур
2020-11-30 Добавлена схема клавиатуры для БК05
2020-12-01 Q64, M05: перекомпонованы схемы, all: исправлены ошибки в клавиатурах
2023-06-19 Добавлены схемы Q-128 в улучшенном качестве
2023-06-19 DD, M05, Q64, Q128: проекты KiCad обновлены до версии 7.0
2023-06-19 Q128: исправлен проект KiCad
2023-06-19 Q128+: Выделена схема Кворум-128+
2023-06-19 Q128+: Добавлены фотографии
2023-12-30 m-05: Добавлено руководство по эксплуатации Magic 5
